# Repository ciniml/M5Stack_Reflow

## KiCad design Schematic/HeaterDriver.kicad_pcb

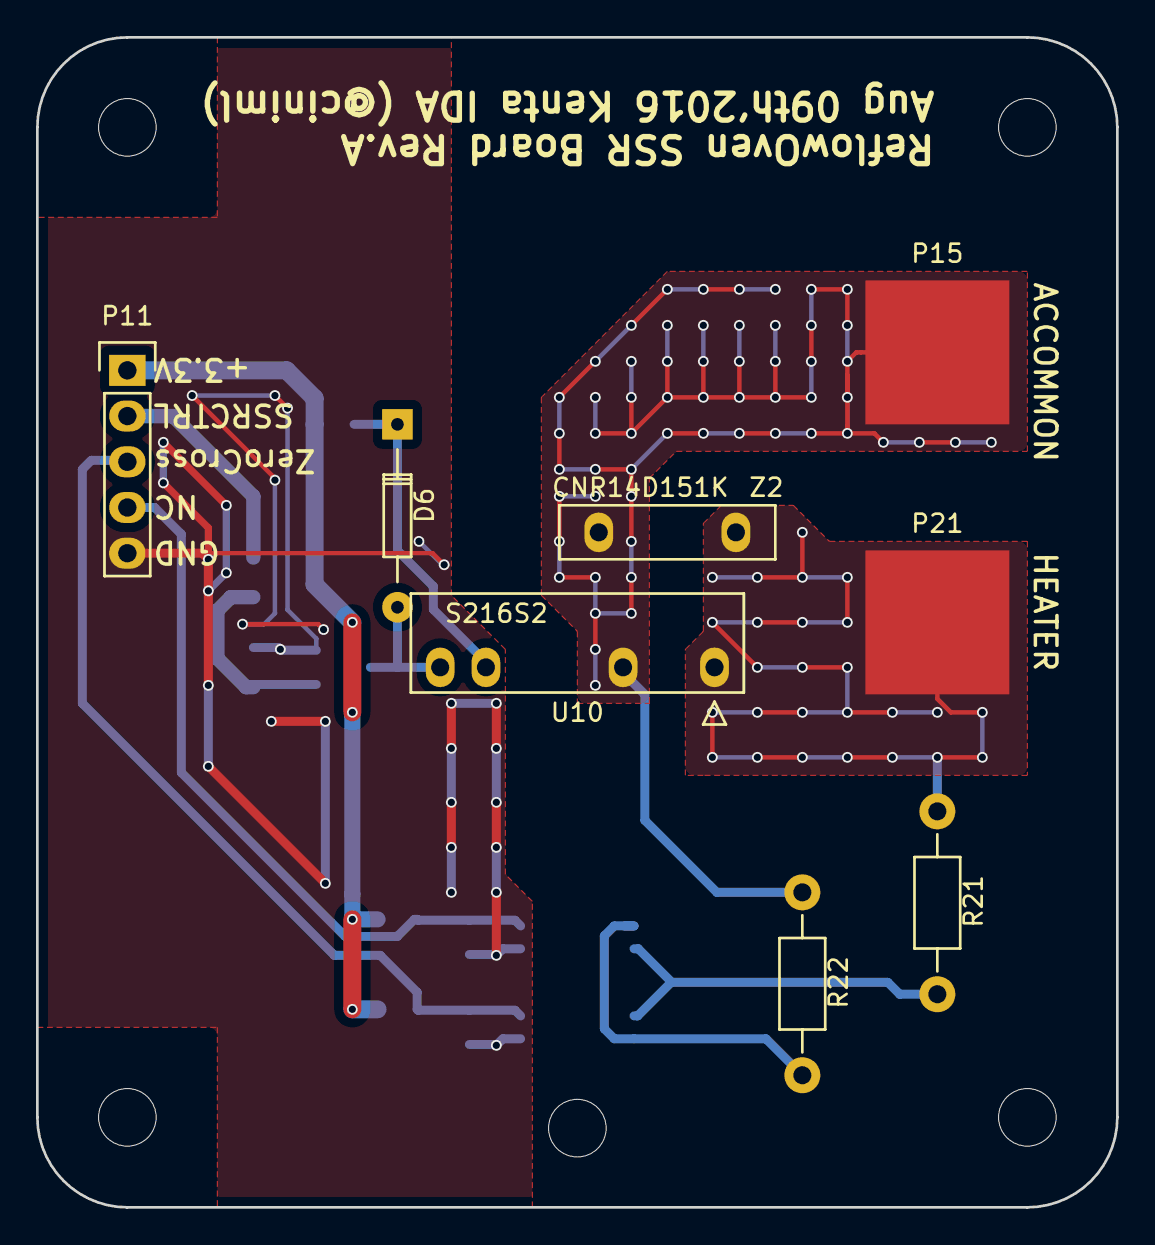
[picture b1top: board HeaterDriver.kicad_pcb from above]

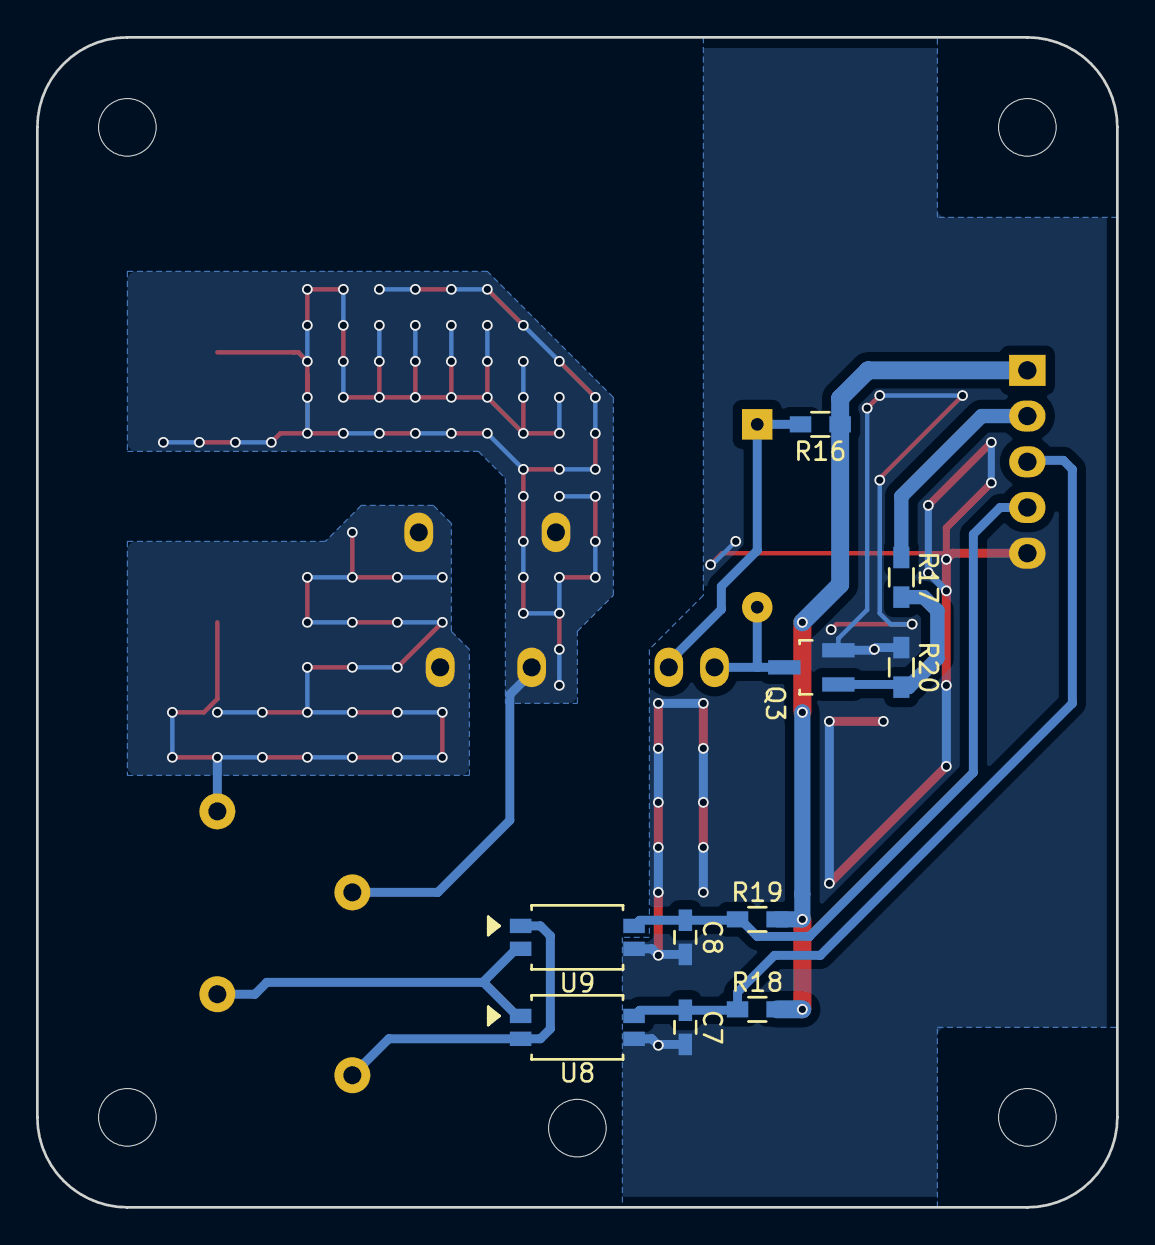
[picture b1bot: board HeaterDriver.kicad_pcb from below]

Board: 2 copper layers, 60.0 x 65.0 mm, 18 parts (10 on the bottom side), 12 nets.

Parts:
C7, C8: 100n; C_0603_HandSoldering
D6: 1N4148; Diode_DO-35_SOD27_Horizontal_RM10
P11: CONN_01X05; Pin_Header_Straight_1x05
P15, P21: PV-3
Q3: IRLML6344TRPBF; SOT-23_Handsoldering
R16: 200; R_0603_HandSoldering
R17: 100; R_0603_HandSoldering
R18, R19: 1k; R_0603_HandSoldering
R20: 10k; R_0603_HandSoldering
R21, R22: 47k, 1/2; Resistor_Horizontal_RM10mm
U8, U9: TLP291; SO4
U10: S216S2; S216S02-BEND-HEATSINK
Z2: CNR14D151K

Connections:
/HEATERDRIVER2/AC_COMMON: P15.1, R22.1, U10.2, Z2.1
/HEATERDRIVER2/GND_LOGIC: C7.2, C8.2, P11.5, Q3.2, R20.1, U8.3, U9.3
/HEATERDRIVER2/HEATER: P21.1, R21.1, U10.1, Z2.2
/HEATERDRIVER2/SSR_CTRL: P11.2, R17.1
/HEATERDRIVER2/VDD_LOGIC: P11.1, R16.1, R18.2, R19.2
/HEATERDRIVER2/ZC_OUT_A: C7.1, P11.3, R18.1, U8.4
/HEATERDRIVER2/ZC_OUT_B: C8.1, P11.4, R19.1, U9.4
unnamed: D6.1, R16.2, U10.3
unnamed: D6.2, Q3.3, U10.4
unnamed: Q3.1, R17.2, R20.2
unnamed: R21.2, U8.1, U9.2
unnamed: R22.2, U8.2, U9.1

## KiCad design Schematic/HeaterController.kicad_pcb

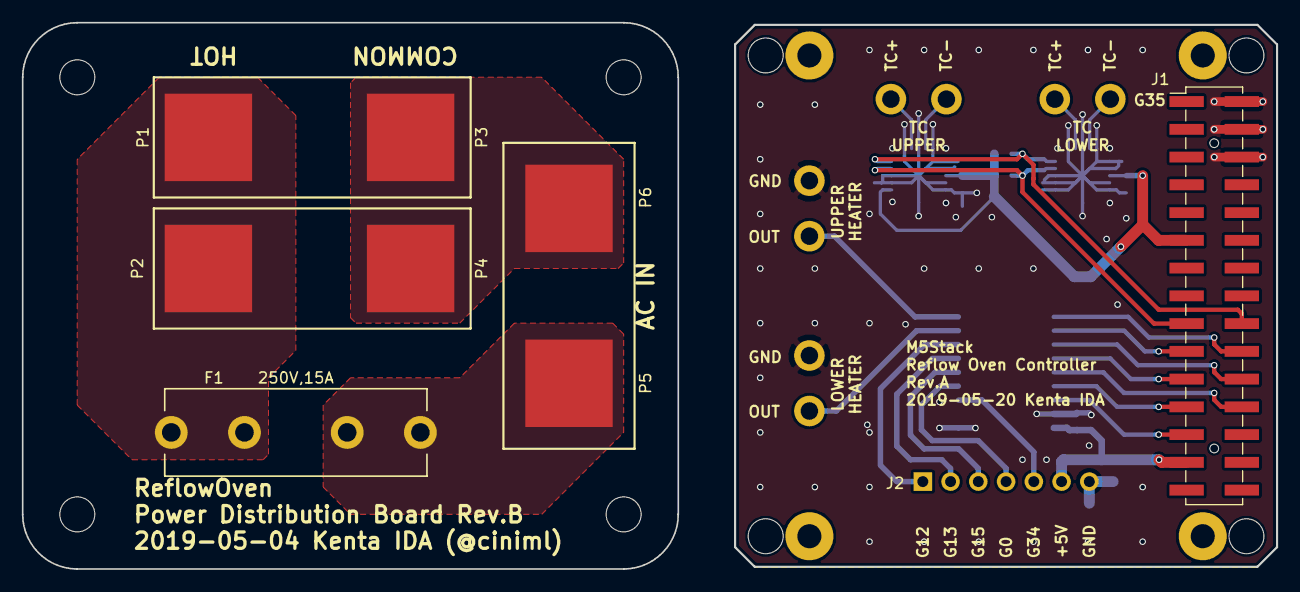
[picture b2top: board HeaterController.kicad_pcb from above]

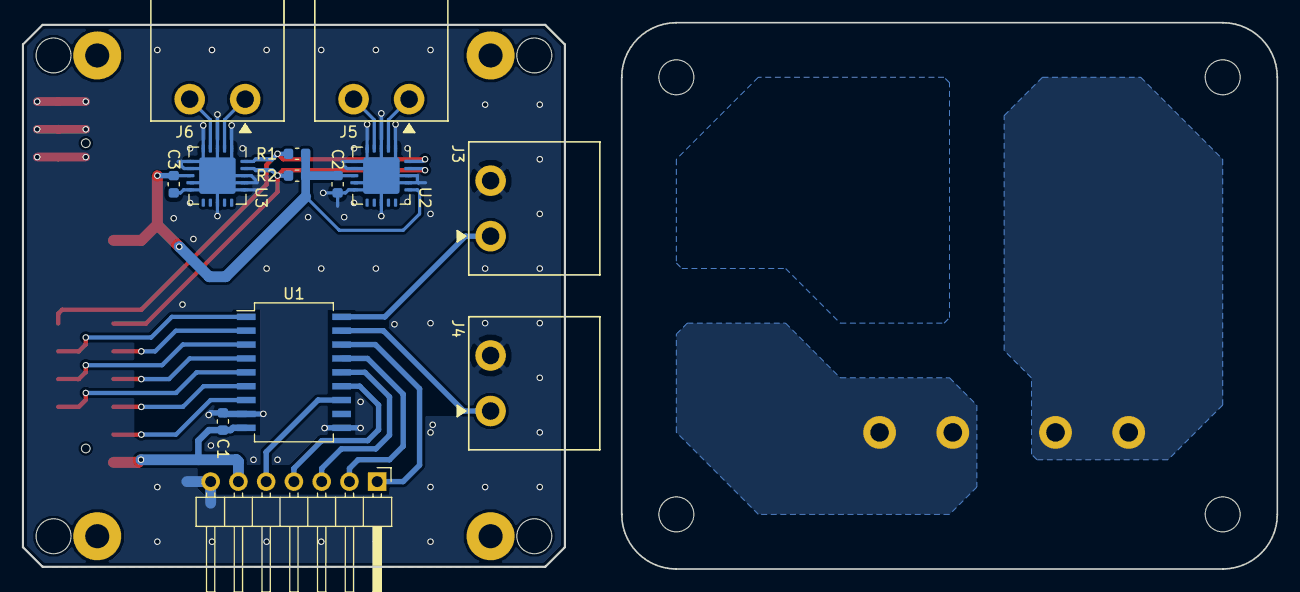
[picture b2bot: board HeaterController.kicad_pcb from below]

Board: 2 copper layers, 114.8 x 50.0 mm, 33 parts (13 on the bottom side), 26 nets.

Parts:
C1, C2, C3: 100n; C_0603_1608Metric
F1: 250V,15A; FUC-03A-FUSE-20
J1: MBUS_TOP; MBUS_Header
J2: Conn_01x07; PinHeader_1x07_P2.54mm_Horizontal
J3, J4, J5, J6: ETB43024G000Z; ETB43XX2
MH1, MH2, MH3, MH4, MH5, MH6, MH7, MH8: Corner; MountingHole_3.2mm_M3
MH9, MH10, MH11, MH12: Corner; MountingHole_2.2mm_M2_Pad
P1, P2, P3, P4, P5, P6: PV-3
R1, R2: NC; R_0603_1608Metric
U1: TBD62783A; SOP-18_7.0x12.5mm_P1.27mm
U2, U3: MCP9600; QFN-20-1EP_5x5mm_P0.65mm_EP3.35x3.35mm

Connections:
+3V3: C2.2, C3.2, J1.11, R1.1, R2.1, U2.8, U2.16, U3.8
+5V: C1.2, J1.27, J2.6, U1.9
/EXTERNAL0: J2.1, U1.16
/EXTERNAL1: J2.2, U1.15
/EXTERNAL2: J2.3, U1.14
/EXTERNAL3: J2.4, U1.13
/EXTERNAL4: J2.5, U1.12
/GPIO_G2: J1.20, U1.1
/GPIO_G5: J1.19, U1.2
/IIS_IN: J1.25, U1.7
/IIS_MK: J1.23, U1.6
/IIS_OUT: J1.24, U1.5
/IIS_SK: J1.22, U1.3
/IIS_WS: J1.21, U1.4
/SCL: J1.17, R2.2, U2.19, U3.19
/SDA: J1.18, R1.2, U2.20, U3.20
/SSRCTRL_LOWER: J4.1, U1.17
/SSRCTRL_UPPER: J3.1, U1.18
GND: C1.1, C2.1, C3.1, J1.2, J1.4, J1.6, J2.7, J3.2, J4.2, U1.8, U1.10, U2.1, U2.3, U2.5, U2.6, U2.7, U2.9, U2.10, U2.13, U2.17, U2.18, U2.21, U3.1, U3.3, U3.5, U3.6, U3.7, U3.9, U3.10, U3.13, U3.16, U3.17, U3.18, U3.21
unnamed: F1.1, P1.1, P2.1
unnamed: F1.2, P5.1
unnamed: J5.1, U2.2
unnamed: J5.2, U2.4
unnamed: J6.1, U3.2
unnamed: J6.2, U3.4
unnamed: P3.1, P4.1, P6.1

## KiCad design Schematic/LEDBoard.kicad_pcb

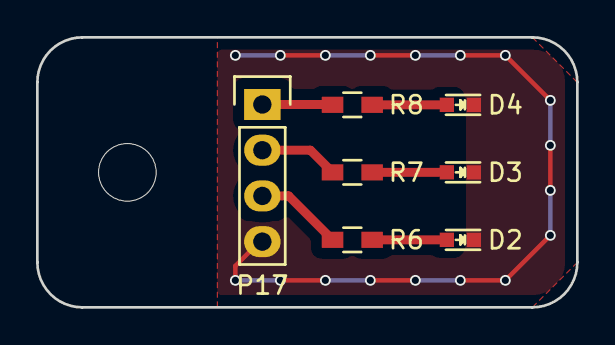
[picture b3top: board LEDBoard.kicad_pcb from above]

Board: 2 copper layers, 30.0 x 15.0 mm, 7 parts (0 on the bottom side), 7 nets.

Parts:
D2: BLUE; LED_0603
D3: RED; LED_0603
D4: GREEN; LED_0603
P17: CONN_01X04; Pin_Header_Straight_1x04
R6: 100; R_0603_HandSoldering
R7: 470; R_0603_HandSoldering
R8: 200; R_0603_HandSoldering

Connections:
unnamed: D2.1, D3.1, D4.1, P17.4
unnamed: D2.2, R6.2
unnamed: D3.2, R7.2
unnamed: D4.2, R8.2
unnamed: P17.1, R8.1
unnamed: P17.2, R7.1
unnamed: P17.3, R6.1

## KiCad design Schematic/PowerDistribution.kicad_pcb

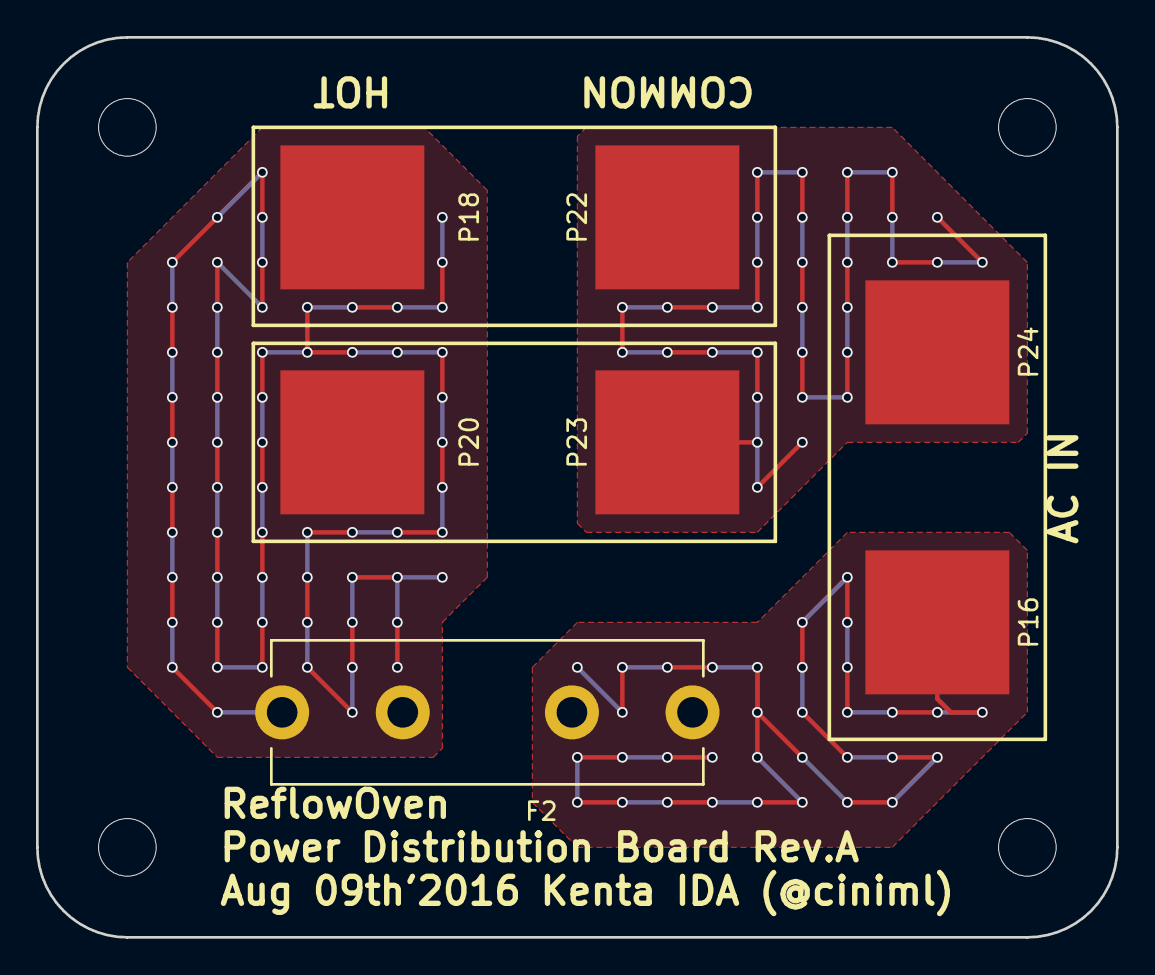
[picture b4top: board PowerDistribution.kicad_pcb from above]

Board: 2 copper layers, 60.0 x 50.0 mm, 7 parts (0 on the bottom side), 3 nets.

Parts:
F2: 250V,15A; FUC-03A-FUSE-20
P16, P18, P20, P22, P23, P24: PV-3

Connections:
unnamed: F2.1, P18.1, P20.1
unnamed: F2.2, P16.1
unnamed: P22.1, P23.1, P24.1

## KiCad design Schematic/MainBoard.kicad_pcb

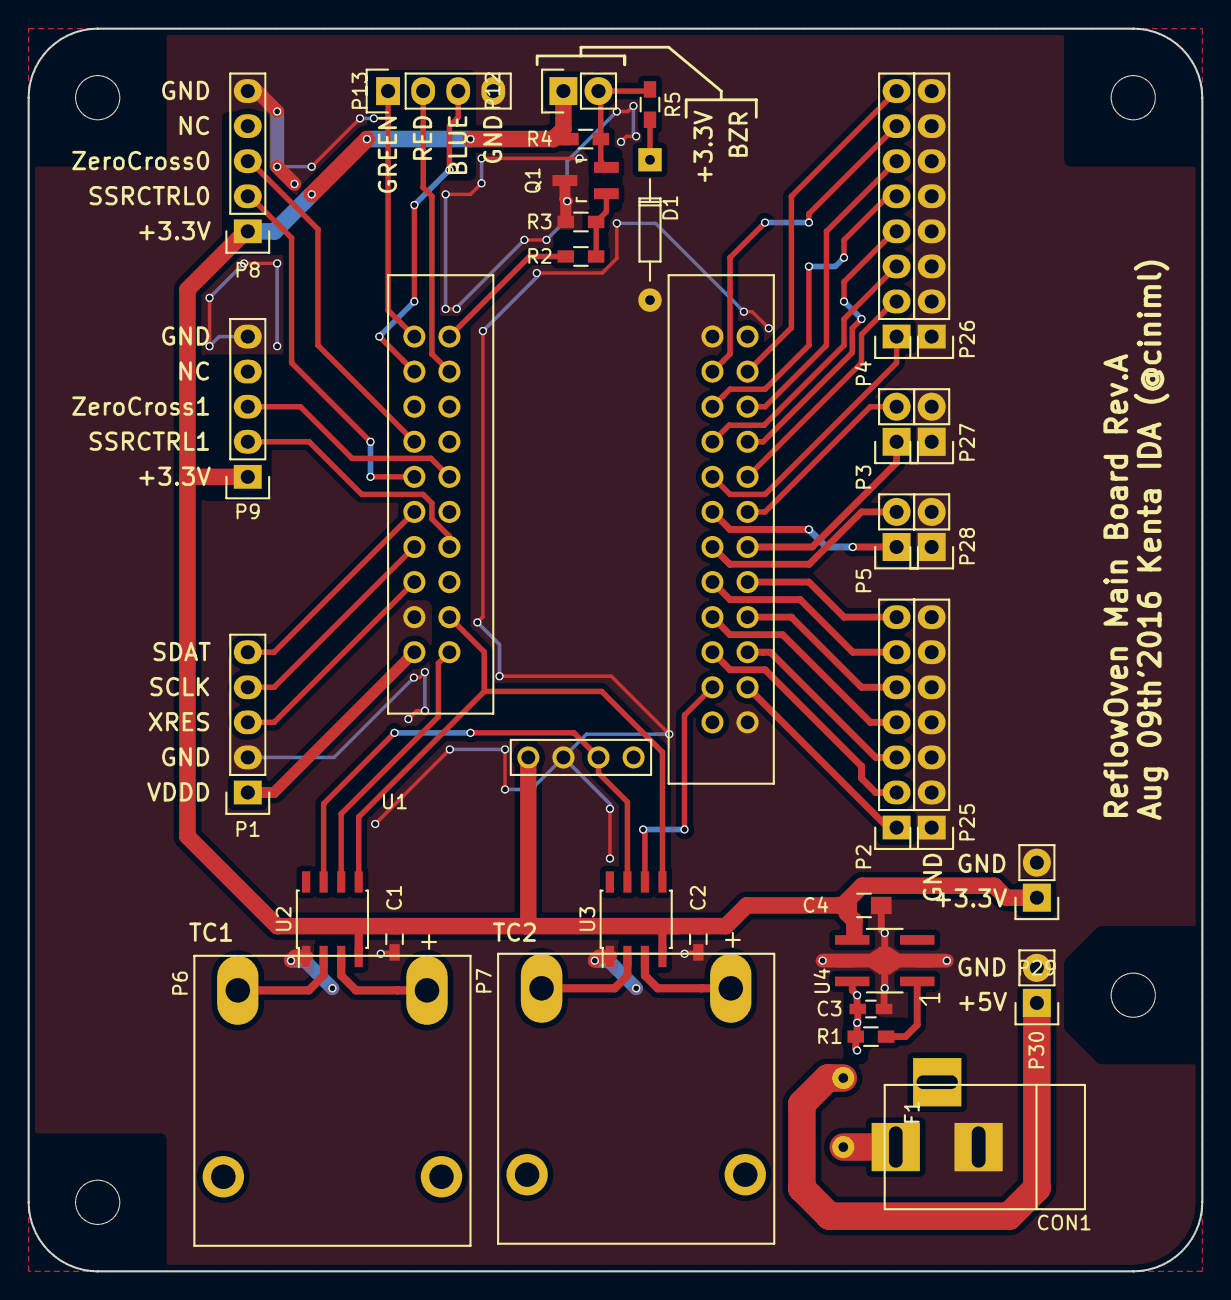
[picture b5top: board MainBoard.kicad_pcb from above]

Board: 2 copper layers, 85.0 x 90.0 mm, 34 parts (0 on the bottom side), 47 nets.

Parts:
C1, C2: 100n; C_0603_HandSoldering
C3: 330n; C_0603_HandSoldering
C4: 10u,6.3V; C_0805_HandSoldering
CON1: BARREL_JACK
D1: 5.1V; Diode_DO-35_SOD27_Horizontal_RM10
F1: 500mA; RXEF050
P1, P8, P9: CONN_01X05; Pin_Header_Straight_1x05
P2, P25: CONN_01X07; Pin_Header_Straight_1x07
P3, P5, P12, P27, P28, P29, P30: CONN_01X02; Pin_Header_Straight_1x02
P4, P26: CONN_01X08; Pin_Header_Straight_1x08
P6, P7: PCC-SMP
P13: CONN_01X04; Pin_Header_Straight_1x04
Q1: 2N7002; SOT-23_Handsoldering
R1, R3: 10k; R_0603_HandSoldering
R2: 100; R_0603_HandSoldering
R4: 1k; R_0603_HandSoldering
R5: 470; R_0603_HandSoldering
U1: CY8CKIT-142
U2, U3: MAX31855KASA; SOIC-8_3.9x4.9mm_Pitch1.27mm
U4: NJM2884U1-33; SOT89-5_Housing_Handsoldering

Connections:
+3V3: C1.2, C2.2, C4.2, P8.1, P9.1, P12.1, P29.1, R4.2, U1.VDD, U2.4, U3.4, U4.4
+5V: C3.2, F1.2, P30.1, R1.1, U4.5
/Buzzar: R2.2, U1.0.0
/CS0: U1.1.6, U2.6
/CS1: U1.2.0, U3.6
/LedBlue: P13.3, U1.0.3
/LedGreen: P13.1, U1.0.1
/LedRed: P13.2, U1.0.2
/MISO: U1.1.5, U2.7, U3.7
/SCK: U1.1.7, U2.5, U3.5
/SSRCtrl0: P8.2, U1.1.2
/SSRCtrl1: P9.2, U1.1.3
/ZeroCross0: P8.3, U1.1.0
/ZeroCross1: P9.3, U1.1.1
GND: C1.1, C2.1, C3.1, C4.1, CON1.2, D1.2, P1.2, P8.5, P9.5, P13.4, P25.1, P25.2, P25.3, P25.4, P25.5, P25.6, P25.7, P26.1, P26.2, P26.3, P26.4, P26.5, P26.6, P26.7, P26.8, P27.1, P27.2, P28.1, P28.2, P29.2, P30.2, Q1.3, R3.1, U1.GND, U2.1, U3.1, U4.2
unnamed: CON1.1, F1.1
unnamed: D1.1, R5.1
unnamed: P1.1, U1.VDDD
unnamed: P1.3, U1.XRES
unnamed: P1.4, U1.0.7
unnamed: P1.5, U1.0.6
unnamed: P2.1, U1.2.1
unnamed: P2.2, U1.2.2
unnamed: P2.3, U1.2.3
unnamed: P2.4, U1.2.4
unnamed: P2.5, U1.2.5
unnamed: P2.6, U1.2.6
unnamed: P2.7, U1.2.7
unnamed: P3.1, U1.5.0
unnamed: P3.2, U1.5.1
unnamed: P4.1, U1.3.0
unnamed: P4.2, U1.3.1
unnamed: P4.3, U1.3.2
unnamed: P4.4, U1.3.3
unnamed: P4.5, U1.3.4
unnamed: P4.6, U1.3.5
unnamed: P4.7, U1.3.6
unnamed: P4.8, U1.3.7
unnamed: P5.1, U1.4.0
unnamed: P5.2, U1.4.1
unnamed: P6.+, U2.3
unnamed: P6.-, U2.2
unnamed: P7.+, U3.3
unnamed: P7.-, U3.2
unnamed: P12.2, Q1.2, R4.1, R5.2
unnamed: Q1.1, R2.1, R3.2
unnamed: R1.2, U4.1

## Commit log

2019-04-23 Add MCP9600 driver
2019-04-23 Add read_temperatures method
2019-04-23 Add comments
2019-04-29 Implement reflow controller
2021-09-05 Add all materials
